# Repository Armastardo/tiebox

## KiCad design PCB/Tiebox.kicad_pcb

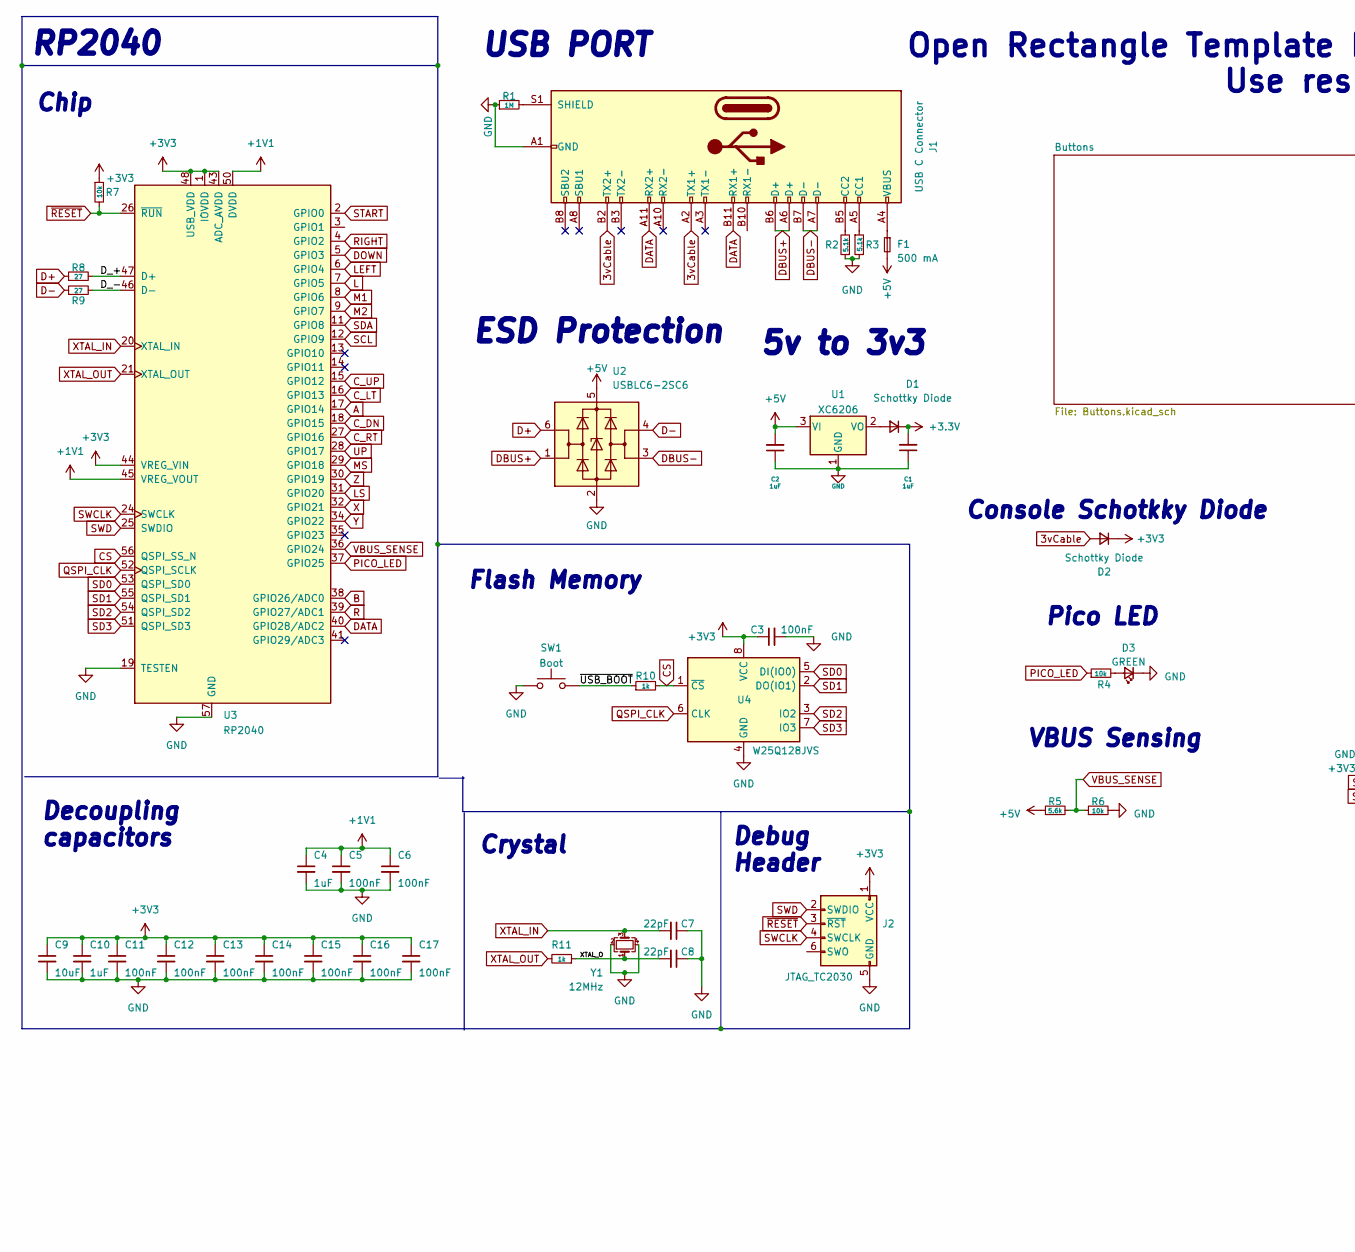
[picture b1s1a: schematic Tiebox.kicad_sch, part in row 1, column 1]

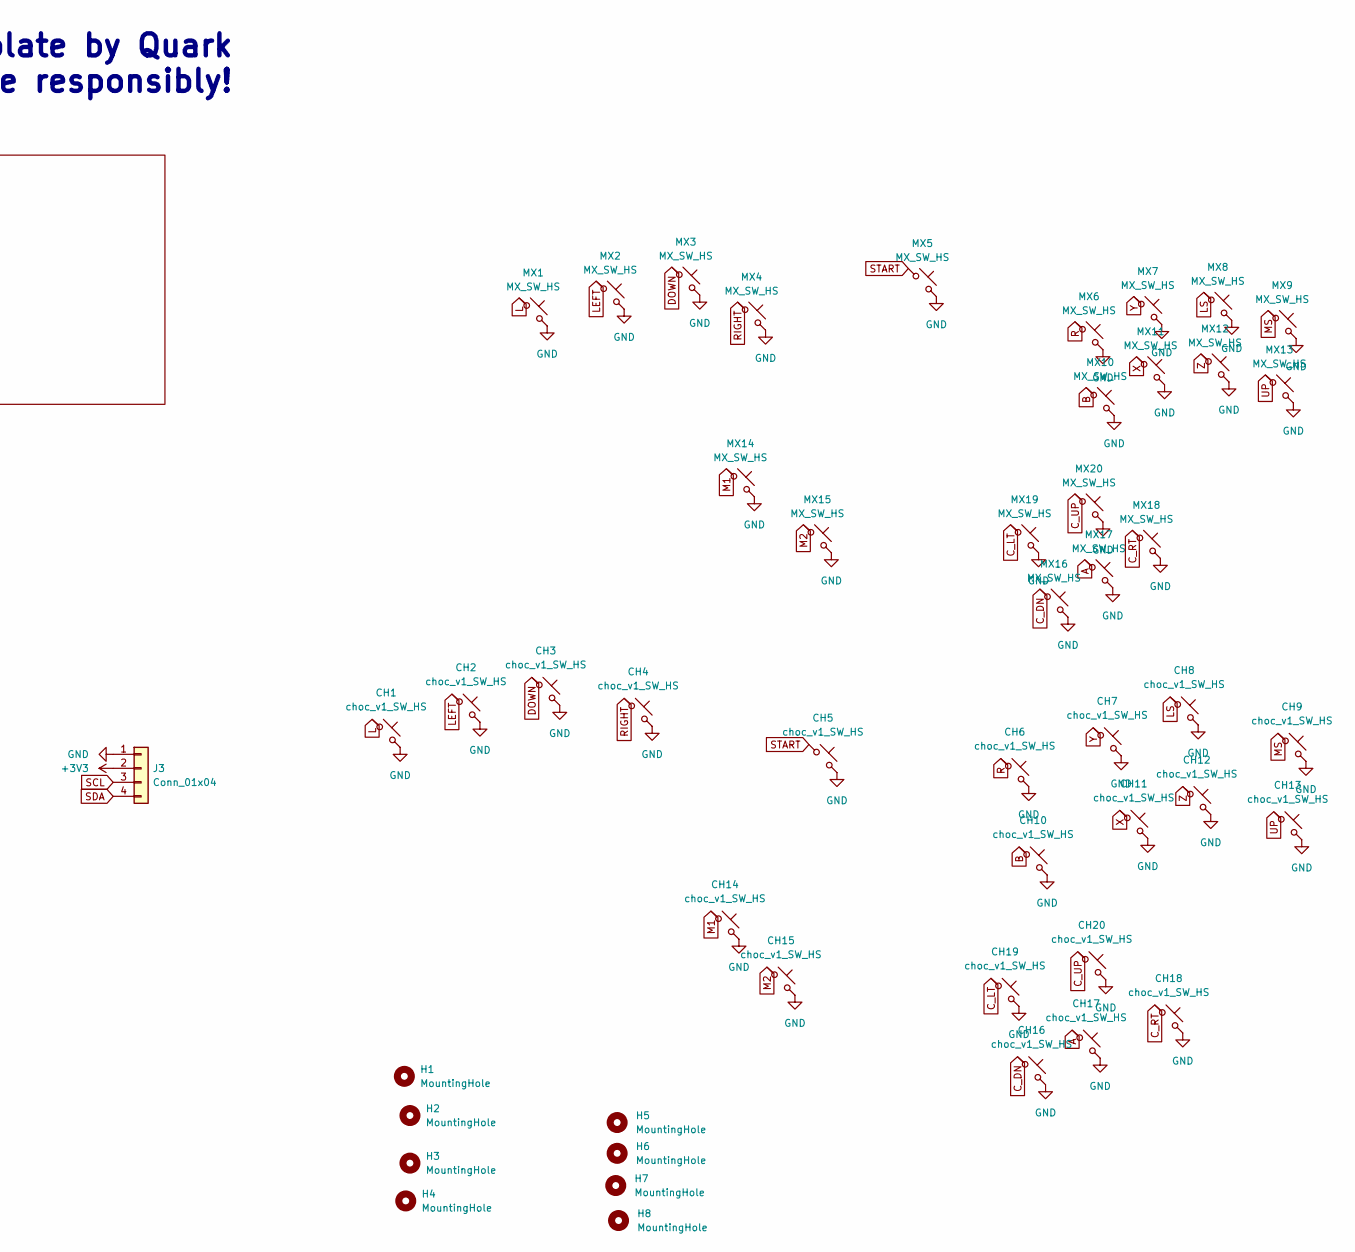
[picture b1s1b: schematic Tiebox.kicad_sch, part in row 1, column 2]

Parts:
C1, C2, C4, C10: 1uF; C_0402_1005Metric; LCSC C52923
C3, C5, C6, C11, C12, C13, C14, C15, C16, C17: 100nF; C_0402_1005Metric; LCSC C1525
C7, C8: 22pF; C_0402_1005Metric; LCSC C1555
C9: 10uF; C_0402_1005Metric; LCSC C15525
CH1, CH2, CH3, CH4, CH5, CH6, CH7, CH8, CH9, CH10, CH11, CH12, CH13, CH14, CH15, CH16, CH17, CH18, CH19, CH20: choc_v1_SW_HS; SW_choc_v1_HS_CPG135001S30_1u
D1, D2: Schottky Diode; D_SOD-123; LCSC C8598
D3: GREEN; LED_0805_2012Metric; LCSC C2297
F1: 500 mA; Fuse_1206_3216Metric; LCSC C70076
H1, H2, H3, H4: MountingHole; MountingHole_3.2mm_M3
H5, H6: MountingHole; qw new logo silk + copper md
H7, H8: MountingHole; 1999 logo md
J1: USB C Connector; TYPE-C_24P_QCHT; LCSC C456013
J2: JTAG_TC2030; CON_TC2030_outlined
J3: Conn_01x04; PinHeader_1x04_P2.54mm_Vertical
MX1, MX2, MX3, MX4, MX5, MX6, MX7, MX8, MX9, MX10, MX11, MX12, MX13, MX14, MX15, MX16, MX17, MX18, MX19, MX20: MX_SW_HS; SW_MX_HS_CPG151101S11_1u
R1: 1M; R_0603_1608Metric; LCSC C22935
R2, R3: 5.1k; R_0402_1005Metric; LCSC C25905
R4, R7: 10k; R_0402_1005Metric; LCSC C25744
R5: 5.6k; R_0603_1608Metric; LCSC C23189
R6: 10k; R_0603_1608Metric; LCSC C25804
R8, R9: 27; R_0603_1608Metric; LCSC C25190
R10, R11: 1k; R_0402_1005Metric; LCSC C11702
SW1: Boot; SW_SPST_SKQG_WithStem; LCSC C318884
U1: XC6206; SOT-23; LCSC C5446
U2: USBLC6-2SC6; SOT-23-6; LCSC C7519
U3: RP2040; RP2040-QFN-56; LCSC C2040
U4: W25Q128JVS; SOIC-8_5.23x5.23mm_P1.27mm; LCSC C97521
Y1: 12MHz; Crystal_SMD_3225-4Pin_3.2x2.5mm; LCSC C9002

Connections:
3vCable: D2.2 (A), J1.A2 (TX1+), J1.B2 (TX2+)
+1V1: C4.1, C5.1, C6.1, U3.23 (DVDD), U3.45 (VREG_VOUT), U3.50 (DVDD)
+5V: C2.2, F1.2, R5.1, U1.3 (VI), U2.5 (VBUS)
/D_+: R8.2, U3.47 (D+)
/D_-: R9.2, U3.46 (D-)
/XTAL_O: C8.2, R11.1, Y1.1
/~USB_BOOT: R10.1, SW1.2
A: CH17.1, MX17.1, U3.17 (GPIO14)
B: CH10.1, MX10.1, U3.38 (GPIO26/ADC0)
CS: R10.2, U3.56 (QSPI_SS_N), U4.1 (~CS)
C_DN: CH16.1, MX16.1, U3.18 (GPIO15)
C_LT: CH19.1, MX19.1, U3.16 (GPIO13)
C_RT: CH18.1, MX18.1, U3.27 (GPIO16)
C_UP: CH20.1, MX20.1, U3.15 (GPIO12)
D+: R8.1, U2.6 (I/O1)
D-: R9.1, U2.4 (I/O2)
DATA: J1.A11 (RX2+), J1.B11 (RX1+), U3.40 (GPIO28/ADC2)
DBUS+: J1.A6 (D+), J1.B6 (D+), U2.1 (I/O1)
DBUS-: J1.A7 (D-), J1.B7 (D-), U2.3 (I/O2)
DOWN: CH3.1, MX3.1, U3.5 (GPIO3)
GND: C1.1, C2.1, C3.2, C4.2, C5.2, C6.2, C7.1, C8.1, C9.2, C10.2, C11.2, C12.2, C13.2, C14.2, C15.2, C16.2, C17.2, CH1.2, CH2.2, CH3.2, CH4.2, CH5.2, CH6.2, CH7.2, CH8.2, CH9.2, CH10.2, CH11.2, CH12.2, CH13.2, CH14.2, CH15.2, CH16.2, CH17.2, CH18.2, CH19.2, CH20.2, D3.1 (K), J1.A1 (GND), J1.A12 (GND), J1.B1 (GND), J1.B12 (GND), J2.5 (GND), J3.1, MX1.2, MX2.2, MX3.2, MX4.2, MX5.2, MX6.2, MX7.2, MX8.2, MX9.2, MX10.2, MX11.2, MX12.2, MX13.2, MX14.2, MX15.2, MX16.2, MX17.2, MX18.2, MX19.2, MX20.2, R1.1, R2.1, R3.2, R6.2, SW1.1, U1.1 (GND), U2.2 (GND), U3.19 (TESTEN), U3.57 (GND), U4.4 (GND), Y1.2, Y1.4
L: CH1.1, MX1.1, U3.7 (GPIO5)
LEFT: CH2.1, MX2.1, U3.6 (GPIO4)
LS: CH8.1, MX8.1, U3.31 (GPIO20)
M1: CH14.1, MX14.1, U3.8 (GPIO6)
M2: CH15.1, MX15.1, U3.9 (GPIO7)
MS: CH9.1, MX9.1, U3.29 (GPIO18)
unnamed: D1.2 (A), U1.2 (VO)
unnamed: D3.2 (A), R4.2
unnamed: F1.1, J1.A4 (VBUS), J1.A9 (VBUS), J1.B4 (VBUS), J1.B9 (VBUS)
unnamed: J1.A5 (CC1), R3.1
unnamed: J1.B5 (CC2), R2.2
unnamed: J1.S1 (SHIELD), R1.2
PICO_LED: R4.1, U3.37 (GPIO25)
QSPI_CLK: U3.52 (QSPI_SCLK), U4.6 (CLK)
R: CH6.1, MX6.1, U3.39 (GPIO27/ADC1)
RIGHT: CH4.1, MX4.1, U3.4 (GPIO2)
SCL: J3.3, U3.12 (GPIO9)
SD0: U3.53 (QSPI_SD0), U4.5 (DI(IO0))
SD1: U3.55 (QSPI_SD1), U4.2 (DO(IO1))
SD2: U3.54 (QSPI_SD2), U4.3 (IO2)
SD3: U3.51 (QSPI_SD3), U4.7 (IO3)
SDA: J3.4, U3.11 (GPIO8)
START: CH5.1, MX5.1, U3.2 (GPIO0)
SWCLK: J2.4 (SWCLK), U3.24 (SWCLK)
SWD: J2.2 (SWDIO), U3.25 (SWDIO)
UP: CH13.1, MX13.1, U3.28 (GPIO17)
VBUS_SENSE: R5.2, R6.1, U3.36 (GPIO24)
X: CH11.1, MX11.1, U3.32 (GPIO21)
XTAL_IN: C7.2, U3.20 (XTAL_IN), Y1.3
XTAL_OUT: R11.2, U3.21 (XTAL_OUT)
Y: CH7.1, MX7.1, U3.34 (GPIO22)
Z: CH12.1, MX12.1, U3.30 (GPIO19)
~RESET: J2.3 (~RST), R7.2, U3.26 (~RUN)

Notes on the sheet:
Console Schotkky Diode
Crystal
USB PORT
Flash Memory
Pico LED
Open Rectangle Template by Quark Use responsibly!
RP2040
Debug Header
VBUS Sensing
Chip
5v to 3v3
ESD Protection
Decoupling capacitors

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
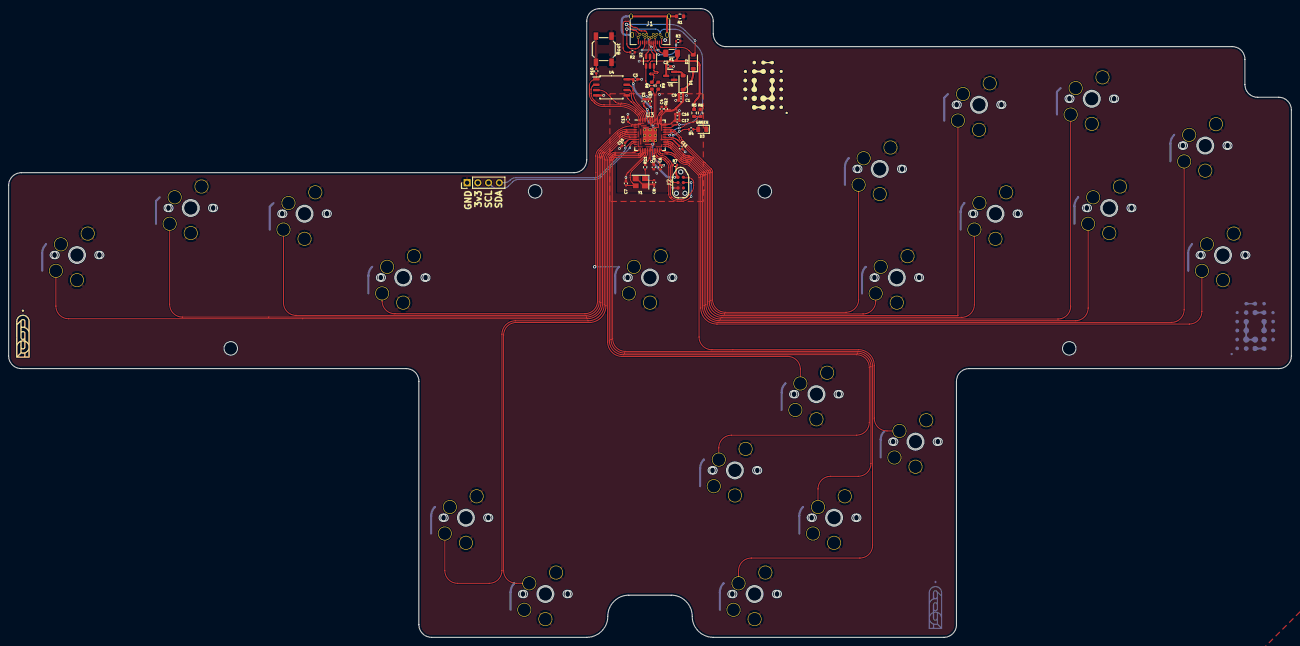
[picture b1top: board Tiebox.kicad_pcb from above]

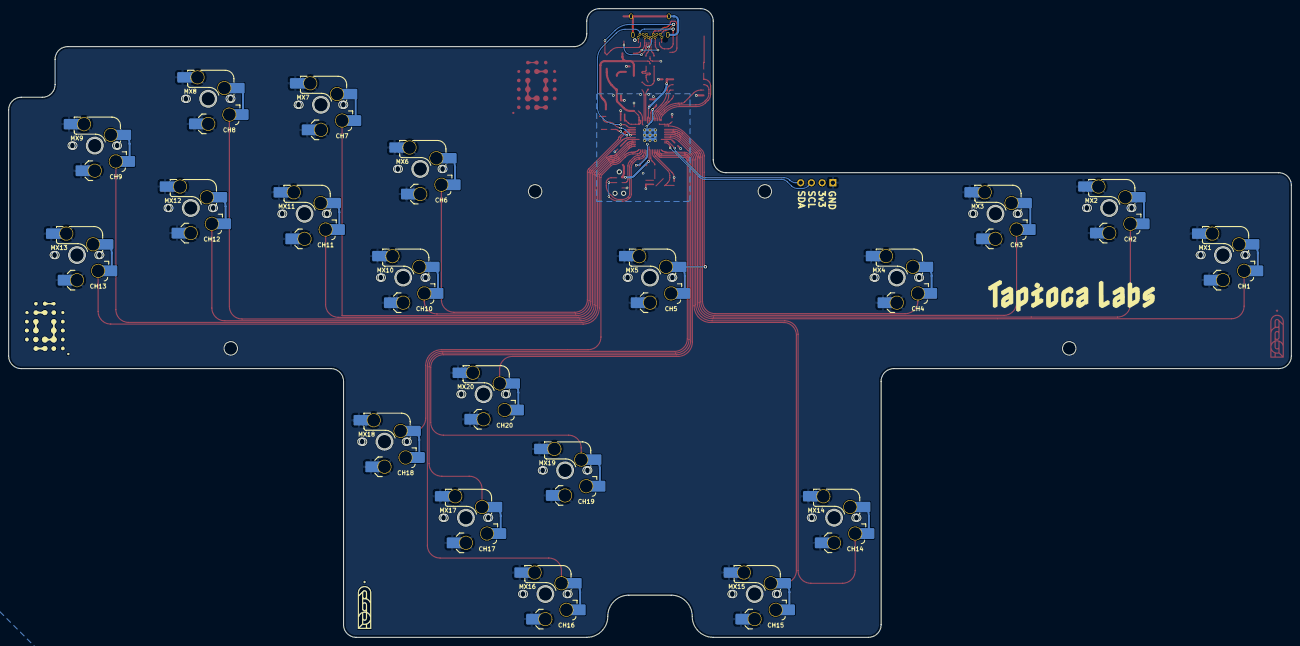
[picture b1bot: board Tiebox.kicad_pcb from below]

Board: 2 copper layers, 304.0 x 149.0 mm, 89 parts (42 on the bottom side), 55 nets.

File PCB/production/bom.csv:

Designator,Footprint,Quantity,Value,LCSC Part #
"C1, C10, C2, C4",0402,4,1uF,C52923
"C11, C12, C13, C14, C15, C16, C17, C3, C5, C6",0402,10,100nF,C1525
"C7, C8",0402,2,22pF,C1555
C9,0402,1,10uF,C15525
"CH1, CH10, CH11, CH12, CH13, CH14, CH15, CH16, CH17, CH18, CH19, CH2, CH20, CH3, CH4, CH5, CH6, CH7, CH8, CH9",SW_choc_v1_HS_CPG135001S30_1u,20,choc_v1_SW_HS,
"D1, D2",D_SOD-123,2,Schottky Diode,C8598
D3,0805,1,GREEN,C2297
F1,1206,1,500 mA,C70076
J1,TYPE-C_24P_QCHT,1,USB C Connector,C456013
"MX1, MX10, MX11, MX12, MX13, MX14, MX15, MX16, MX17, MX18, MX19, MX2, MX20, MX3, MX4, MX5, MX6, MX7, MX8, MX9",SW_MX_HS_CPG151101S11_1u,20,MX_SW_HS,
R1,0603,1,1M,C22935
"R10, R11",0402,2,1k,C11702
"R2, R3",0402,2,5.1k,C25905
"R4, R7",0402,2,10k,C25744
R5,0603,1,5.6k,C23189
R6,0603,1,10k,C25804
"R8, R9",0603,2,27,C25190
SW1,SW_SPST_SKQG_WithStem,1,Boot,C318884
U1,SOT-23,1,XC6206,C5446
U2,SOT-23-6,1,USBLC6-2SC6,C7519
U3,RP2040-QFN-56,1,RP2040,C2040
U4,SOIC-8_5.23x5.23mm_P1.27mm,1,W25Q128JVS,C97521
Y1,Crystal_SMD_3225-4Pin_3.2x2.5mm,1,12MHz,C9002

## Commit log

2024-03-06 Initial component placement
2024-03-11 v1 3d model
2024-03-11 removed locked files
